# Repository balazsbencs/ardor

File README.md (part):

<h1 align="center">
  
</h1>

Ardor is a standalone Raspberry Pi guitar-processing platform with a realtime
audio engine, touchscreen/footswitch UI, preset storage, a browser-based manager
served by the device, and a reproducible Buildroot firmware image.

The signal chain supports Neural Amp Modeler `.nam` files, cabinet impulse
responses, 35 hosted modulation/delay/reverb effects, compression, noise
gating, five-band parametric EQ with high-pass and low-pass filters, global gain,
and a safety limiter. The same
LVGL interface runs in the SDL desktop simulator and on the Raspberry Pi Touch
Display 2.

The pedal is an appliance rather than a plugin host. Plugin formats and an OTA
update workflow are outside the current scope.

<table>
  <tr>
    <td width="50%"></td>
    <td width="50%"></td>
  </tr>
  <tr>
    <td align="center"><sub>Build the chain from neural amps, cabs and effects</sub></td>
    <td align="center"><sub>Four-track looper on the footswitches</sub></td>
  </tr>
</table>

## What You Need

To build an Ardor pedal, start with a Raspberry Pi 4 (the 1 GB model is
enough), its USB-C power supply, and a microSD card for the Ardor image. Put
the Raspberry Pi Codec Zero audio board on top of the Pi, and connect the 5 inch
Raspberry Pi Touch Display 2 with its ribbon cable. A guitar cannot connect
directly to the Codec Zero, so you also need the small Ardor guitar input buffer
board. You can order it from JLCPCB with the parts already fitted (see
[Guitar Input Buffer](#guitar-input-buffer)), and it runs from a normal 9 V
guitar pedal power supply. For a complete floor pedal, add four momentary
footswitches, one rotary knob (encoder) for the master volume, one 1/4 inch
input jack, two 1/4 inch output jacks, and a case. You can 3D print the case
from [`enclosure.openscad`](enclosure.openscad). You need a soldering iron for
some basic soldering of the jacks, switches, and wires. MIDI and expression
pedal inputs come later. The [hardware assembly guide](docs/hardware-assembly.md)
shows all the wiring.

## Community

See [CONTRIBUTING.md](CONTRIBUTING.md) before proposing changes. Contributors
are recognized in [CONTRIBUTORS.md](CONTRIBUTORS.md), and suspected
vulnerabilities should be reported privately according to
[SECURITY.md](SECURITY.md).

## Requirements

- CMake 3.20+
- C++20 compiler
- Single-precision FFTW development files (`libfftw3-dev` on Debian/Ubuntu,
  `brew install fftw` on macOS). Custom SDK paths can be supplied through
  `ARDOR_FFTW_INCLUDE_DIR` and `ARDOR_FFTW_LIBRARY` at CMake configure.
- Git access during CMake configure, for `miniaudio` and `NeuralAmpModelerCore`
- SDL2 for the LVGL desktop simulator (`ARDOR_UI_BACKEND=sdl`)
- macOS for desktop testing, or Linux for target-style builds
- Optional: Go for the manager daemon, Node.js 24 via `nvm use` for the manager
  web app, and Docker for the Buildroot firmware image
- Local test assets:
  - `models/test.nam`
  - `irs/test.wav`
  - optional `reverb-irs/test.wav`
  - optional dry input WAV for offline rendering

Real `.nam` and IR files are ignored by git. Keep licensed/user-provided assets local unless redistribution is allowed.

The POG3 DSP links FFTW, which is GPL-2.0-or-later. Distribution of FFTW-linked
binaries must comply with that license; the repository's MIT license does not
cover FFTW. See [the FFT backend notes](docs/pog3-fft-backend-evaluation.md).

## Guitar Input Buffer

A passive guitar must pass through the Ardor input buffer before it reaches
the Codec Zero. The repository contains the separate, minimal KiCad project
in [`buffer/`](buffer/).

You can order a board with the SMD parts fitted through
[JLCPCB](https://jlcpcb.com/). Upload these files from
[`buffer/jlcpcb/production_files/`](buffer/jlcpcb/production_files/):

- [`GERBER-buffer.zip`](buffer/jlcpcb/production_files/GERBER-buffer.zip) for the PCB files.
- [`BOM-buffer.csv`](buffer/jlcpcb/production_files/BOM-buffer.csv) for the parts list.
- [`CPL-buffer.csv`](buffer/jlcpcb/production_files/CPL-buffer.csv) for the part placement list.

The production files do not include audio jacks, wires, connectors, or the
enclosure. Add these parts after the board arrives. Connect the guitar jack to
`GUITAR_IN` and connect `GUITAR_OUT` to the Codec Zero input. Follow the buffer
schematic for power and ground connections.

## Preset Storage

Preset files live under the data root in bank/slot folders, for example:

- `presets/bank-000/preset-0.json`

Block assets inside preset JSON stay relative to that same data root, such as `models/clean.nam`, `irs/open-back.wav`, or `reverb-irs/small-room.wav`. Cabinet IRs and convolution reverb IRs use separate directories. Existing convolution presets that reference an installed `irs/` asset remain compatible, while new reverb selections use `reverb-irs/`. Absolute paths and `..` traversal are rejected. Real `.nam` models and IRs stay local and are not committed unless redistribution is allowed.

Convolution reverb exposes **Reverb time** in the pedal and manager editors.
It scales the recorded decay from 25% to 100%; 100% preserves the original IR.
For example, a two-second decay becomes approximately one second at 50%.
The processor estimates RT60 from the loaded stereo IR and applies a decay
envelope without changing reflection timing, pitch, or embedded pre-delay.
IRs shorter than 100 ms, silent impulses, and responses without a reliable
decay estimate stay unchanged. The four-second IR cap still applies.
Live edits crossfade using the existing convolution history. This control is
shared across scenes; convolution-kernel preparation runs on the control thread.

### Scenes

Version-4 presets contain four named scenes. A scene changes prepared parameter
values, qualified effect bypass states, input gain, WDW lane values, and a
post-rig trim without rebuilding the audio engine. Each scene can switch
instantly or transition over 0.1–10 seconds.

On a scene-enabled preset, hold FS3 + FS4 for 600 ms to enter or leave the
Scenes layer. The four footswitches then recall the four scene plates. Hold
FS1 + FS2 for one second to open the muted tuner. The touchscreen and Manager
show the live scene separately from the scene being edited.

Qualified delay and reverb blocks offer shared **Cut** and **Let ring** bypass
policies. Let ring stops new wet input while the existing decay continues for a
bounded lifetime. Version-4 data survives preset copies, backup/restore, hosted
read/write, and Looper source snapshots. Explicit flattening resolves one scene,
folds its trim into output gain, removes scene-only mappings, and produces the
minimum compatible ordinary preset version. See
[`presets/bank-002/preset-1.json`](presets/bank-002/preset-1.json) for an
asset-free example.

### Supported Parameters

Preset globals:

- `global.inputGainDb`: input gain before NAM.
- `global.outputGainDb`: output gain after cab.
- `global.safetyLimitDb`: limiter ceiling, where `-1.0` is the default. Stored and applied, but not editable from the UI — it is a protective clipper, not a tone control.

NAM block params:

- `params.inputMode`: stereo-to-mono routing at the NAM input: `"sum"` averages left and right (default), `"left"` uses the left/mono channel, and `"right"` uses the right channel.
- `params.useNano`: when `true`, selects the embedded nano submodel to reduce CPU usage; missing or `false` selects the full model.

Pass `--input-reference-dbu DBU` to map the audio interface's measured analog
input reference to NAM models that contain `input_level_dbu` metadata. The
reference is the analog dBu RMS level that produces a 0 dBFS-peak 1 kHz sine at
the ADC. Models without the metadata retain unity input scaling. Preset input
gain remains available as a separate creative or corrective control.

Cab block params:

- `params.levelDb`: cab level before output gain.
- `params.mix`: `0.0` dry after-NAM signal, `1.0` full cab signal.

Dual Amp is one draggable `type: "dualAmp"` block with two fixed parallel
lanes. Both lanes receive the selected mono input; the left NAM → IR lane feeds
only the left output and the right NAM → IR lane feeds only the right output.
It uses:

- `params.inputMode`: `"sum"` (default), `"left"`, or `"right"`.
- `params.leftNamAsset` / `params.rightNamAsset`: relative `.nam` asset paths.
- `params.leftIrAsset` / `params.rightIrAsset`: relative IR asset paths.
- `params.leftUseNano` / `params.rightUseNano`: per-model nano selection.
- `params.leftCabLevelDb` / `params.rightCabLevelDb`: `-60..12` dB.
- `params.leftCabMix` / `params.rightCabMix`: `0.0..1.0`.
- `params.leftPolarityInvert` / `params.rightPolarityInvert`: whole-lane polarity.

An enabled Dual Amp block cannot be combined with standalone NAM or cabinet
blocks in the same preset. Existing version-1 serial presets remain compatible.

Dual Rig generalizes that fixed block to two independent child chains. It is a
version-2 preset block and remains one draggable item in the outer chain:

```json
{
  "version": 2,
  "blocks": [{
    "id": "rig-1",
    "type": "dualRig",
    "enabled": true,
    "asset": "",
    "params": {
      "inputMode": "sum",
      "leftLevelDb": 0,
      "leftPolarityInvert": false,
      "rightLevelDb": 0,
      "rightPolarityInvert": false
    },
    "lanes": {
      "left": { "blocks": [
        {"id":"left-nam","type":"nam","enabled":true,"asset":"models/clean.nam","params":{}},
        {"id":"left-cab","type":"cab","enabled":true,"asset":"irs/open.wav","params":{}},
        {"id":"left-chorus","type":"mod","enabled":true,"asset":"","params":{"mode":"chorus"}}
      ]},
      "right": { "blocks": [
        {"id":"right-nam","type":"nam","enabled":true,"asset":"models/crunch.nam","params":{}},
        {"id":"right-cab","type":"cab","enabled":true,"asset":"irs/closed.wav","params":{}},
        {"id":"right-delay","type":"delay","enabled":true,"asset":"","params":{"mode":"digital"}}
      ]}
    }
  }]
}
```

Both lanes receive the same selected mono input. Each lane is processed in its
declared order; the left lane's left output and the right lane's right output
are retained at the fixed merge. Child block IDs are globally unique, both
lanes must be non-empty, and split blocks cannot be nested. Version-1 presets
and the fixed `dualAmp` block remain supported.

Daisy effect blocks use no asset path and store catalog-defined normalized
`0.0..1.0` parameters. The built-in catalog currently contains 35 modes:

- 13 modulation/special effects: chorus, flanger, rotary, vibe, phaser,
  vintage/pattern tremolo, poly octave, auto swell, filter, formant,
  quadrature, and destroyer.
- 10 delays: digital, tape, dual, filter, lo-fi, bucket-brigade, duck,
  pattern, swell, and tremolo.
- 12 reverbs: room, hall, plate, spring, bloom, cloud, shimmer, chorale,
  nonlinear, swell, magneto, and reflections.

Each mode uses semantic labels, physical-value formatting, defaults, and
discrete choices from `src/daisyfx/DaisyFxCatalog.cpp`. Compressor blocks use
`type: "dynamics"` with mode `compressor`.

Noise Gate blocks use `type: "dynamics"` with mode `noise_gate`. Their numeric
parameters are `threshold_db`, `reduction_db`, `attack_ms`, `hold_ms`,
`release_ms`, `hysteresis_db`, and `sidechain_hpf_hz`. Detection is
stereo-linked and the gate adds no lookahead latency.

The Ardor-maintained Daisy effect engine lives under `src/daisyfx/hosted/`.
Its upstream origin and license are preserved there; host adaptation and effect
implementation now live together under `src/daisyfx/`.

Five-band EQ blocks use `type: "eq"`, mode `parametric_eq_5`, and five entries
in `params.bands`. Each band stores `enabled`, `frequency_hz` (20–20,000 Hz),
`q` (0.1–18), and `gain_db` (-18 to +18 dB). Missing fields receive indexed
band defaults; saved presets always contain exactly five complete bands. The
surrounding `high_pass` and `low_pass` filters store `enabled`, `frequency_hz`,
`q`, and `slope_db_per_octave` (6, 12, 18, or 24; default 12).

## Build

Desktop build with the SDL UI:

```sh
cmake -S . -B build-sdl -DARDOR_UI_BACKEND=sdl -DCMAKE_BUILD_TYPE=Release
cmake --build build-sdl -j
```

Primary executables include:

- `build-sdl/pedal-poc` — offline/realtime engine and integrated UI
- `build-sdl/pedal-ui-sim` — desktop-only LVGL simulator
- `build-sdl/audio-probe` — audio-device probe

An opt-in standalone desktop application is being developed for Mac first.
Configure with `-DARDOR_BUILD_DESKTOP=ON` and the SDL backend to build
`ardor-desktop` (`Ardor.app` on Mac). See the
[desktop prototype instructions](apps/ardor-desktop/README.md) for audio setup,
user-library storage, validation, and current limitations.

The full-chain [CLAP beta](plugins/ardor-clap/README.md) is an optional follow-up
with `-DARDOR_BUILD_CLAP_PLUGIN=ON`. It supports 48 kHz DAW sessions and
per-project full-chain state. Beta 2 includes the shared Ardor editor on Mac
with `-DARDOR_UI_BACKEND=memory`; Linux uses host-generated controls. It is
separate from the Whammy plugin.

The [standalone NAM loader](plugins/nam-clap/README.md) provides a smaller CLAP
effect for macOS Apple Silicon, with a native editor for the model's own controls
and selectable Nano/Standard tiers when exported together. Build it separately
with `cmake -S plugins/nam-clap -B build-nam-clap -DCMAKE_BUILD_TYPE=Release`.

For a headless build, configure with `-DARDOR_UI_BACKEND=none`. The Pi firmware
uses the `fbdev` backend through the Buildroot package.

## Test

```sh
ctest --test-dir build-sdl --output-on-failure
```

The CTest suite covers preset parsing and activation, realtime-chain behavior,
Daisy effects and automation, compressor, noise gate, parametric EQ, the
four-track looper and its persistent store, tuner and control gestures, UI
models/LVGL interaction, audio-device enumeration, and reload stress. The
looper timing benchmark is intentionally separate from CTest:

```sh
cmake --build build-sdl --target pedal-looper-bench
./build-sdl/pedal-looper-bench --block-sizes 64,128 --warmup 100 --iterations 1000
```

Host results are useful for regressions, but do not replace the Raspberry Pi 4
acceptance benchmark and ten-minute production-backend soak. Hardware latency,
Codec Zero routing, and subjective audio validation remain device-level checks.

## List Audio Devices

```sh
./build-sdl/pedal-poc --devices
```

On macOS with a Behringer U-Phoria UMC22, it usually appears as `USB Audio CODEC`.

## Offline Render

Preset files use relative asset paths under `--data-root`.

Preset-driven offline render:

```sh
./build-sdl/pedal-poc \
  --offline \
  --preset ./presets/bank-000/preset-0.json \
  --data-root . \
  --input ./dryguitar.wav \
  --output ./wet.wav
```

Bypass NAM and test only IR/output rendering:

```sh
./build-sdl/pedal-poc \
  --offline \
  --ir irs/test.wav \
  --input /path/to/dry-guitar.wav \
  --output /tmp/ardor-wet.wav \
  --bypass-nam
```

Run NAM plus IR:

```sh
./build-sdl/pedal-poc \
  --offline \
  --model models/test.nam \
  --ir irs/test.wav \
  --input /path/to/dry-guitar.wav \
  --output /tmp/ardor-wet.wav
```

Input and IR WAV files must be 48 kHz.

## Realtime Run

List devices first:

```sh
./build-sdl/pedal-poc --devices
```

Example output:

```text
Playback devices:
  [1] USB Audio CODEC
Capture devices:
  [1] USB Audio CODEC
```

Run with explicit UMC22 routing:

```sh
./build-sdl/pedal-poc \
  --realtime \
  --model models/test.nam \
  --ir irs/test.wav \
  --sample-rate 48000 \
  --block-size 64 \
  --capture-device 1 \
  --playback-device 1 \
  --input-channel right \
  --output-channel both \
  --input-gain-db -12 \
  --output-gain-db -6 \
  --safety-limit-db -1
```

Preset-driven realtime run:

```sh
./build-sdl/pedal-poc \
  --realtime \
  --preset ./presets/bank-000/preset-0.json \
  --data-root . \
  --capture-device 1 \
  --playback-device 1 \
  --input-channel left \
  --output-channel both \
  --block-size 64 \
  --ir-samples 8192
```

Stop with `Ctrl-C`.

### Realtime preset slot switching

Slot-based realtime mode loads presets from `--data-root`:

```sh
./build-sdl/pedal-poc --realtime --data-root . --bank 0 --slot 0 \
  --capture-device 1 --playback-device 1 --input-channel left --output-channel both \
  --block-size 64 --ir-samples 8192
```

While it is running, type `0`, `1`, `2`, or `3`, then Enter, to switch presets in the current bank. The app reloads outside the audio callback, restarts the realtime device, and resumes telemetry.

Use `--input-channel left` for input 1 and `--input-channel right` for input 2. On the UMC22, the instrument input is commonly the right/second capture channel.

Realtime mode uses the full IR by default through partitioned convolution. Use `--ir-samples N` to cap long IRs when comparing performance or testing slower hardware.

The output safety limiter is on by default at `-1 dBFS`; adjust it with `--safety-limit-db DB` or disable it with `--no-safety-limit`.

If the sound is overloaded, reduce `--input-gain-db` first. That lowers the signal before NAM. If the amp character is right but the final output clips, reduce `--output-gain-db`.

Add `--clip-debug` to print interval peaks at the input-gain boundary, after every effect block, and immediately before the safety limiter. For example:

```text
levels input=-7.2dBFS nam:amp=1.4dBFS CLIP[38] ir:cab=-0.8dBFS output=-1.1dBFS limiter=[122] first=nam:amp
```

`CLIP[n]` counts frames above 0 dBFS during the interval, and `first=` identifies the earliest boundary that crossed full scale. This distinguishes signal-level overload from intentional NAM distortion: if `input` or `nam:...` is first, reduce input gain; if `ir:...` is first, reduce cabinet level; if only `output` or `limiter` is active, reduce output gain or master volume. The meter observes processor boundaries—it cannot label the intentional nonlinear distortion inside a NAM model as clipping.

With `--clip-debug --ui`, the touchscreen status bar shows the same diagnosis: red `CLIP` with the first stage and peak, amber `LIMIT` when only the safety limiter engages, or green `LEVEL OK`. It refreshes once per second.

Realtime status prints once per second:

```text
callbacks=28125 over=0 over%=0.00 max=0.41ms avg=0.23ms budget=1.33ms
```

`over` counts callbacks that took longer than the audio budget. For `--block-size 64` at 48 kHz, the callback budget is about `1.33 ms`.

Dual Amp and Dual Rig always have a sequential fallback: the callback processes
the complete left lane and then the complete right lane. On a four-core Pi,
enable the optimized path with
`--parallel-rigs --audio-cpu 2 --rig-worker-cpu 3`. This keeps the callback at
`SCHED_FIFO/70` on CPU 2 and runs a persistent right-lane worker at
`SCHED_FIFO/69` on CPU 3; the callback processes the complete left lane
concurrently and joins the worker once at the fixed merge. Effects before and
after the parallel block still run serially on the callback thread. The two CPU
arguments are required and must differ. If the worker cannot obtain its
requested realtime policy or affinity, the rig reports the failure and uses
sequential processing. The older `--parallel-dual-amp` and
`--dual-amp-worker-cpu` spellings remain accepted.

The Buildroot image enables that layout by default through
`PARALLEL_RIGS=1`, `AUDIO_CPU=2`, and `RIG_WORKER_CPU=3` in
`/etc/ardor-pedal.env`. WDW adds two independent lane workers; the image
defaults to `WDW_DRY_WORKER_CPU=0` and `WDW_WET_WORKER_CPU=1` and passes them as
`--wdw-dry-worker-cpu` / `--wdw-wet-worker-cpu`. These assignments keep the
audio callback, legacy dual-rig worker, and both WDW lanes on distinct Pi 4
cores. The UI and non-audio work remain normal-priority Linux tasks; the
realtime DSP threads preempt them on their assigned cores.

Measure that layout on a running pedal over SSH:

```sh
./scripts/measure-device-performance.sh --duration 30 192.168.88.17
```

The probe reports whole-core utilization and headroom, per-thread CPU usage,
last CPU, affinity, realtime policy and priority, migrations, temperature, and
CPU clock range. Production builds also publish an atomic snapshot at
`/run/ardor-pedal.telemetry`; the probe uses its before/after counters to check
callback overruns, scheduling gaps, parallel-worker deadline misses,
non-finite DSP blocks, block-size mismatches, and overload bypass. It checks
that the callback is `SCHED_FIFO/70` on CPU 2. With a Dual Amp or Dual Rig
preset active, require and validate the `SCHED_FIFO/69` worker on CPU 3:

```sh
./scripts/measure-device-performance.sh \
  --duration 60 --require-worker 192.168.88.17
```

The local wrapper streams
`scripts/device-performance-remote.sh` to BusyBox `sh`; it does not install
anything or modify the pedal. Use `ARDOR_PI_HOST`, `ARDOR_SSH_USER`, and
`ARDOR_SSH_OPTS` for repeatable lab configuration. Passwords are handled by
OpenSSH and are never stored by the scripts. The final pass/fail verdict covers
thread placement, realtime scheduling, and audio/DSP fault counters;
utilization, headroom, clock, and thermal values remain measurements to compare
between presets and builds.

Realtime telemetry is shared between CLI and UI. The known-good baseline remains `--block-size 64 --ir-samples 8192`. If the overload bypass latches, the CLI prints `bypassed=1` and the UI shows `BYPASS`.

First target settings:

- sample rate: `48000`
- preferred block size: `64`
- fallback block size: `128`
- input: mono
- output: stereo
- round-trip latency goal: under `10 ms`

Chain layout contract: NAM and cabinet blocks are mono stages. A NAM block may follow
stereo effects and folds its input according to `params.inputMode`; its mono output is
copied to both channels. Cabinet blocks must still precede stereo effects. Dual Amp
and Dual Rig establish stereo with their hard-left/hard-right lanes. Inside a Dual
Rig, the same ordering rules apply independently to each lane. Modulation preserves
stereo input. The hosted delay and reverb effects preserve the stereo dry field but
sum their wet input to mono before producing their vendor-defined stereo wet output.

Hardware controls on Raspberry Pi use Linux input events:

```sh
./build-sdl/pedal-poc --realtime --data-root . --bank 0 --slot 0 \
  --control-device /dev/input/event-footswitches \
  --control-device /dev/input/event-encoder \
  --block-size 64 --ir-samples 8192
```

The app maps `KEY_F1` through `KEY_F4` to preset slots and relative encoder
movement to master output volume. Tap FS1 through FS4 to select the matching
slot. Hold FS2 for 600 ms to move down one bank, or FS4 for 600 ms to move up
one bank; bank changes keep the current slot number. Hold the two left switches
(`KEY_F1` + `KEY_F2`) together for one second to mute the output and open the
tuner; press any footswitch to exit without changing presets. The touchscreen
provides the same tuner flow through the preset-screen Tuner button and
tuner-screen Exit button.

### Four-Track Looper

Select a preset, then press **Looper** on the preset screen. That preset remains
locked until the loop session is closed, and all recorded audio captures its
processed stereo output before master volume and the safety limiter. The four
large track plates select the working track. The four footswitches keep fixed
performance roles:

- FS1 toggles one-level undo/redo for the selected track;
- tap FS2 to select the next track, or hold it to clear the selected track;
- FS3 starts/stops the first recording or an overdub, and FS4 mutes/unmutes the
  selected track;
- hold FS1 + FS2 to pause and enter the tuner; leaving the tuner resumes a loop
  that was previously running;
- later empty tracks arm and begin recording together at the next master-loop
  boundary, so all four layers stay synchronized;
- the touchscreen adds global pause/resume, New/Save/Load/Close, track
  selection, and per-track level/balance controls.

Save and Load are available only while paused. A saved set contains the four
effective stereo tracks, mix settings, loop length, and a snapshot of the
source preset under `loops/<32-character-id>/`. Saving runs outside the audio
callback and publishes the manifest last, so a failed replacement preserves
the previous durable revision. Closing a session releases its preset lock and
restores the preset that was active before a recalled loop.

The planned TRS-A MIDI and expression-pedal interface, message mapping, GPIO
allocation, and preset expression schema are documented in
[`docs/midi-expression-control.md`](docs/midi-expression-control.md). Its
native KiCad schematic is under [`hardware/control-io`](hardware/control-io/README.md).

## Manager Daemon

The REST manager daemon lives in `services/managerd`. It manages `.nam`, `.wav`,
and preset files without doing management work in the realtime process. Asset
uploads queue a catalog refresh for the pedal UI. Applying a saved slot queues
a live engine swap, handled by the pedal management loop without restarting the
audio process; a short muted transition protects the active audio callback.

The hosted HTTPS manager architecture and delivery plan are specified in
[`docs/hosted-manager-architecture.md`](docs/hosted-manager-architecture.md).
Its Phase 1 foundation includes the shared UI transport contract, durable
device identity, versioned wire schemas, and a reconnecting outbound cloud
agent. Phase 2 adds a SQLite-backed hosted control plane, account recovery,
device presence, and physically confirmed claiming. Phase 3 adds hosted preset
list/read/save/apply operations with durable idempotency. Phase 4 adds bounded
asset streaming and server-side TONE3000 integration. Phase 5 adds device-local
accounts, recoverable reset flows, and mDNS discovery.

Run locally without auth:

```sh
cd services/managerd
ARDOR_API_AUTH=off \
ARDOR_DATA_ROOT=../.. \
ARDOR_API_BIND=127.0.0.1 \
ARDOR_API_PORT=8080 \
go run ./cmd/ardor-managerd
```

The device status endpoint is:

```sh
curl http://127.0.0.1:8080/api/device
```

The daemon also serves a device-hosted build of the React manager from `/`.
When loaded from the daemon, the manager connects to the same origin
automatically, so any browser on the network can manage the pedal:

```sh
cd apps/manager
nvm use
npm run build:device

cd ../../services/managerd
ARDOR_API_AUTH=off ARDOR_DATA_ROOT=../.. go run ./cmd/ardor-managerd
```

Open `http://127.0.0.1:8080` for local development, or the corresponding
device address on the local network. On supported networks, the daemon also
advertises `_ardor-manager._tcp` and a stable hostname derived from the device
identity. With the default port, use
`http://ardor-<first-8-device-id-characters>.local:8080`; a production image
that binds the daemon to port 80 can omit the port. Set `ARDOR_MDNS=off` only
when discovery must be disabled. The generated bundle is embedded in the
`ardor-managerd` binary so it remains available without internet access.

For repeat LAN deployments, `scripts/deploy-lan.sh` uses a local Docker builder
image (`ardor-builder:ubuntu-24.04`) after its first run, avoiding a fresh APT
installation each time. Normal deploys reuse Buildroot's package output; set
`ARDOR_PEDAL_DIRCLEAN=1` only when a clean pedal-package rebuild is needed.
Use `ARDOR_APT_MIRROR=http://hu.archive.ubuntu.com/ubuntu` to build the cached
image from the Hungarian Ubuntu mirror.

Auth is enabled by default when no environment override is supplied. On first
start, the pedal displays a short-lived setup code. Open the device-hosted
manager on a trusted LAN and enter that code to choose one local username and
password. Passwords are stored as Argon2id hashes; browser sessions use an
`HttpOnly`, `SameSite=Strict` cookie and mutation requests require a matching
local Origin and Host. Direct LAN access uses HTTP, so the UI clearly warns
that it is intended for trusted networks. `ARDOR_API_AUTH=off` is for explicit
development/testing use and no static API token is required.

Set `TONE3000_CLIENT_ID` on the device to enable **Browse TONE3000** under
Assets → NAM models. Ardor supports NAM A2 captures only. The device starts
TONE3000's LAN OAuth relay using its Wi-Fi address, so the browser or phone
used to sign in must be on the same trusted Wi-Fi network as the pedal. OAuth
credentials remain in device memory only for the one 15-minute selection and
the selected model is saved through the normal local asset path. The
publishable `t3k_pub_…` client ID may be deployed on the device; never deploy a
TONE3000 secret key. `TONE3000_BASE_URL` defaults to
`https://www.tone3000.com` and is useful only for development overrides.
LAN deployments preserve an existing TONE3000 configuration. If the client ID
is missing, they restore the firmware's publishable default; set
`TONE3000_CLIENT_ID` when deploying to override it.

The Security & reset settings can sign out, reset only local access, or request
a factory reset. Resetting local access removes the username, password hash,
and all sessions while preserving presets, assets, Wi-Fi, and cloud state. A
factory reset must be approved on the pedal with footswitch 1 (footswitch 4
cancels); it clears device-local user data while preserving the stable device
identity and its reset audit record. A durable reset marker makes an interrupted
factory reset resume deterministically after restart.

The outbound cloud agent is disabled by default. A control-plane deployment can
enable it with `ARDOR_CLOUD_ENABLED=on` and an HTTPS origin in
`ARDOR_CLOUD_URL`. Preset reads are available over an authenticated claimed
device connection. Preset save/apply remains opt-in per pedal with
`ARDOR_CLOUD_REMOTE_MUTATIONS=on`; only the four allowlisted preset operations
are accepted. The generated Ed25519 identity is stored under
`<ARDOR_DATA_ROOT>/identity/device.json` with mode `0600`.

## Hosted Control Plane

The initial control plane in `services/controlplane` is a single Go service
with an embedded migration set and a pure-Go SQLite driver. SQLite is the
intentional first-deployment choice: the server has one active instance and a
single writer, so PostgreSQL would add operations without adding useful
capacity yet. The repository boundary leaves a future database migration open.

Run the API locally over explicitly enabled development HTTP:

```sh
cd services/controlplane
ARDOR_INSECURE_HTTP=on \
ARDOR_PUBLIC_ORIGIN=http://127.0.0.1:8090 \
go run ./cmd/ardor-controlplane
```

Build the hosted browser application with the repository Node version:

```sh
cd apps/manager
nvm use
npm run build:hosted
```

Production deployment must expose that static bundle and `/v1` from the same
public HTTPS origin. Account sessions are `HttpOnly`, `SameSite=Strict`, secure
cookies; state-changing browser requests also require the exact public Origin.
Hosted preset save/apply requests carry UUID idempotency keys; completed
responses and audit events are persisted in the same SQLite transaction.

## Manager Web App

The React manager in `apps/manager` connects to `ardor-managerd` and provides
bank/slot browsing, drag-and-drop chain editing, block validation and
inspection, undo/redo, Save/Apply, asset upload/rename/delete, and light/dark
themes. The device serves it over LAN HTTP, so no installation is needed. There
is no desktop application.

Run the app against a device during development:

```sh
cd apps/manager
npm install
npm run dev
```

TONE3000 browsing of NAM captures is part of the hosted control-plane build.
The control plane holds the TONE3000 credentials; see
`services/controlplane/README.md`.

For local testing, run the Go daemon with auth disabled and use
`http://127.0.0.1:8080` as the manager base URL:

```sh
cd services/managerd
ARDOR_API_AUTH=off ARDOR_DATA_ROOT=../.. ARDOR_API_BIND=127.0.0.1 ARDOR_API_PORT=8080 \
go run ./cmd/ardor-managerd
```

## Legacy UI Mockup

The original static HTML concept remains available for design history:

```sh
open mockups/preset-ui/index.html
```

The LVGL implementation described below is the authoritative interface.

## Touch UI and LVGL Simulator

The touch UI includes:

- A four-slot preset screen with bank controls, master-volume status, Edit,
  direct Tuner entry, and a global Settings gear between **Bank+** and **Edit**.
- A touch-first Settings screen for changing Wi-Fi credentials without
  reflashing, choosing the panel palette, configuring MIDI/expression input,
  and selecting a 32, 64, or 128-sample audio buffer. Audio-buffer changes
  restart the supervised engine process before they take effect.
- A persistent footer with centered master volume and one-second audio-buffer
  headroom feedback calculated from recent callback time versus its deadline.
- A single left-to-right signal canvas with horizontal touch scrolling,
  per-preset scroll memory, dedicated block drag handles, and Input/Output
  jump controls.
- An asset drawer with separate All, Amps, Cabs, Utility, Modulation, Delays,
  and Reverbs filters. Utility contains compressor, Noise Gate, and EQ blocks.
- `+` insertion points between every top-level effect and between effects in
  each split lane. Top-level insertion offers `Split Left / Right`; lane
  insertion prevents nested split regions.
- Compact lane handles reorder effects within a rail or move them across the
  Left and Right rails; moving the final block out of a lane is rejected.
- Dual Rig presets render as an explicit `SPLIT`, separate color-coded `LEFT`
  and `RIGHT` rails, and a stereo `JOIN` instead of disguising routing as an
  ordinary effect card.
- Long chains remain on the same horizontal signal line and auto-scroll when a
  dragged block reaches either screen edge.
- Two-row, three-column parameter pages using large horizontal sliders with
  inline labels/values, plus a matching rectangular bypass control.
- A dedicated five-band parametric EQ editor with high-pass and low-pass stages,
  selectable 6–24 dB/oct slopes, and a live response graph.
- A muted tuner with note/frequency/cents guidance and both touchscreen Exit
  and footswitch exit.

Build and launch the desktop simulator with:

```sh
./scripts/build-sim.sh
```

In Edit mode, tap any `+` on the mono rail and choose **Split Left / Right** to
create a version-2 split region. The Split starts with NAM and IR in both
lanes, using the first installed model and IR when available. Tap a lane's `+`
to add another effect directly to that rail. Only one active Split is
supported, split regions cannot be nested, and existing standalone NAM/IR
blocks must be removed before inserting the Split.

`pedal-ui-sim` is a desktop-only tool. It does not wire footswitch GPIO, the encoder, Codec Zero, or realtime audio. For the integrated UI+audio experience use `pedal-poc --ui` (see below).

### LVGL simulator with preset files

The simulator can load the same preset files used by `pedal-poc`:

```sh
./build-sdl/pedal-ui-sim --data-root . --bank 0
```

It reads:

- `presets/bank-000/preset-0.json`
- `presets/bank-000/preset-1.json`
- `presets/bank-000/preset-2.json`
- `presets/bank-000/preset-3.json`

Built-in algorithms are listed first, then assets discovered from
`models/*.nam`, `irs/*.wav`, and `reverb-irs/*.wav`. Cabinet and
convolution reverb impulses stay in their own drawer categories. Compressor,
Noise Gate, EQ, and Daisy effects come from built-in catalogs. The simulator
saves chain edits only when Save is pressed.

## Integrated UI and Audio

Pass `--ui` to `pedal-poc` in slot mode to run the LVGL UI alongside the audio engine in a single process:

```sh
./build-sdl/pedal-poc \
  --realtime \
  --ui \
  --data-root . \
  --bank 0 --slot 0 \
  --capture-device 1 \
  --playback-device 1 \
  --input-channel left \
  --output-channel both \
  --block-size 64 --ir-samples 8192
```

The UI starts on the preset screen. On-device effect-chain edits preview
immediately: structural and discrete changes prepare and swap a replacement
engine, while supported continuous parameters are published live. Save only
persists the already-audible draft. Switching preset or bank with unsaved edits
asks whether to Save, Discard, or Cancel. Telemetry (callback count, overruns, bypass state) updates once
per second. Encoder master volume is reflected in the UI. Tuner mode shows the
detected note, frequency, cents offset, and flat/sharp guidance while keeping
the pedal output muted.

`--ui` requires `ARDOR_UI_BACKEND=sdl` (desktop default) or `ARDOR_UI_BACKEND=fbdev` (Pi). It has no effect on the non-slot realtime or offline paths.

## Buildroot Firmware Image

The repository contains a Buildroot external tree for a Raspberry Pi 4 pedal
image. The build pins and verifies Buildroot 2025.02.15, runs in a native Docker
container on Apple Silicon or x86_64, and preserves the validated Raspberry Pi
Linux 6.18 hardware stack.

Build the complete image from the repository root:

```sh
./scripts/build-image.sh
```

The resulting `sdcard.img` contains:

- `/usr/bin/ardor-pedal` and `/etc/init.d/S99ardor-pedal`.
- `/usr/bin/ardor-managerd` and `/etc/init.d/S98ardor-managerd`.
- `/etc/ardor-pedal.env`, `/etc/ardor-managerd.env`, and the Codec Zero mixer
  state.
- A read-only root filesystem and writable `/opt/ardor-pedal` data partition
  seeded with four presets.

See [BUILD.md](BUILD.md) for prerequisites, versioned-volume behavior, flashing,
rollback, troubleshooting, hardware checks, REST verification, and deferred
upgrade work.

## Hardware Validation

See [Hardware Assembly Guide](docs/hardware-assembly.md) for the current Codec
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
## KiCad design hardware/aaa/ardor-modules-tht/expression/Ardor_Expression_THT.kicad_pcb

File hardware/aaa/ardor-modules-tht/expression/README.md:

# Passive expression pedal / I2C ADC / HAND ASSEMBLY

T1 hand-assembly PCB: 110 × 85 mm. **Unbuilt engineering prototype.**

[KiCad project](Ardor_Expression_THT.kicad_pro) · [Manual BOM](BOM.csv) · [Schematic](review/schematic.pdf) · [Bare-board Gerbers](assembly/Ardor_Expression_THT-Gerbers.zip)

Fit an **Adafruit product 1085 ADS1115, STEMMA QT revision**, using two six-pin 2.54 mm sockets and mating headers, with the digital VDD/GND/SCL/SDA/ADDR/ALRT row toward the lower edge of the outlined module footprint. The VDD corner is the square carrier pad (U301 pad 8). Two header rows are 12.7 mm apart. Earlier Adafruit boards and generic blue modules have different layouts and are not substitutes. See the complete [breakout pin translation](../SOURCES.md#ads1115-breakout-pin-translation). Do not rotate it 180 degrees.

The purchased breakout already contains all small SMD parts. Only its ordinary header pins require soldering. AVDD/AGND and ALRT are deliberately not wired on the carrier. Leave the breakout's ADDR-to-VDD solder jumper **open**. JP302 must have one shunt: 1–2 selects 0x48, 2–3 selects 0x49. These are the same ADS1115 registers/addresses used by M1; no ADC-driver change is required.

Use a passive 10–100 kΩ expression pot; do not connect powered CV. JP301 needs **two** shunts: 1–3 plus 2–4 for tip wiper, or 3–5 plus 4–6 for ring wiper. TRS sleeve goes to J302.3. Change polarity with power off.

Leave **JP303 and JP304 unshunted initially**. The breakout has permanent onboard 10 kΩ SDA/SCL pull-ups; these jumpers control only the additional carrier 2.2 kΩ pair. With a Raspberry Pi's 1.8 kΩ pair, the effective resistance is approximately 1.53 kΩ before adding any other module. Add the carrier pair only after calculating total bus pull-up current and checking cable rise time. Removing the carrier shunts does not remove the breakout's pull-ups.

Supply 3.3 V / 15 mA. Commission without the breakout first: verify rail polarity at the socket, then fit the breakout and check I²C detection at 100 kHz. Select ±4.096 V PGA and 128 SPS, read AIN0 (wiper) and AIN1 (excitation reference), normalize AIN0/AIN1, calibrate endpoints and smooth. Test both polarity settings and open-cable behavior. Do not drive the pedal while the module is unpowered.

## Connector pin assignments

Directions are relative to this board. Standard header square pads identify pin 1. Read reference and pin numbers from the back silkscreen; mirrored CAD exports are labelled as back views.

### J302 — PASSIVE PEDAL INPUT / EXCITATION OUTPUT

| Pin | Net | Direction | Connect to |
|---|---|---|---|
| 1 | EXP_TIP | INPUT / OUTPUT | Passive expression socket tip; not a powered CV pedal. |
| 2 | EXP_RING | INPUT / OUTPUT | Passive expression socket ring; not a powered CV pedal. |
| 3 | GND | GROUND | TRS sleeve; pedal pot ground and enclosure bond. |

### J101 — 3V3 POWER INPUT + I2C TO HOST

| Pin | Net | Direction | Connect to |
|---|---|---|---|
| 1 | +3V3 | POWER INPUT | Positive output of the matching regulated supply. |
| 2 | GND | GROUND | Host or cable ground / 0 V. |
| 3 | SDA | INPUT / OUTPUT | Host I2C SDA data pin. |
| 4 | SCL | INPUT | Host I2C SCL clock pin. |

### JP301 — JUMPER ONLY: PEDAL POLARITY

| Pin | Net | Direction | Connect to |
|---|---|---|---|
| 1 | EXP_TIP | JUMPER | Fit a shunt to pin 3 for tip-wiper mode. |
| 2 | EXP_RING | JUMPER | Fit a shunt to pin 4 for tip-wiper mode. |
| 3 | EXP_WIPER | INPUT / JUMPER | Shunt 1-3 for tip wiper, or 3-5 for ring wiper. |
| 4 | EXP_EXC | OUTPUT / JUMPER | Shunt 2-4 for tip wiper, or 4-6 for ring wiper. |
| 5 | EXP_RING | JUMPER | Fit a shunt to pin 3 for ring-wiper mode. |
| 6 | EXP_TIP | JUMPER | Fit a shunt to pin 4 for ring-wiper mode. |

TIP: 1-3 + 2-4; RING: 3-5 + 4-6. Use TWO shunts; no external cable.

### JP302 — JUMPER ONLY: ADC ADDRESS

| Pin | Net | Direction | Connect to |
|---|---|---|---|
| 1 | GND | JUMPER | Shunt 1-2 selects address 0x48. |
| 2 | ADDR | CONTROL / JUMPER | Fit ONE shunt: 1-2 or 2-3. |
| 3 | +3V3_A | JUMPER | Shunt 2-3 selects address 0x49. |

1-2: 0x48; 2-3: 0x49. One shunt required; no external cable.

### JP303 — JUMPER ONLY: SDA PULLUP

| Pin | Net | Direction | Connect to |
|---|---|---|---|
| 1 | SDA_PULL | JUMPER | Shunt 1-2 only if the host has no SDA pull-up. |
| 2 | SDA | INPUT / OUTPUT / JUMPER | Same shunt; this is not a host cable connector. |

Fit 1-2 to enable. Remove if host already has a pull-up.

### JP304 — JUMPER ONLY: SCL PULLUP

| Pin | Net | Direction | Connect to |
|---|---|---|---|
| 1 | SCL_PULL | JUMPER | Shunt 1-2 only if the host has no SCL pull-up. |
| 2 | SCL | INPUT / JUMPER | Same shunt; this is not a host cable connector. |

Fit 1-2 to enable. Remove if host already has a pull-up.

## Assembly and files

Fit low-profile axial parts first, then sockets/headers and radial capacitors. Match diode bands, electrolytic polarity and IC notches to the PCB. Install the ICs or ADC breakout last. H1/H2 are 2.2 mm nonplated M2 mounting holes, not electrical terminals. Check enclosure clearance and capacitor/socket height: these boards are larger than M1.

Use the manual BOM and the bare-board Gerber/drill ZIP. There is no SMT assembly order. Front silkscreen shows component references; the front fabrication drawing shows package outlines and orientation; use the BOM for values. Back silk includes port functions and pin numbers. Native checks and package manifests are under `verification/`; they do not replace prototype measurements.

[Assembly accessories](assembly/accessories.csv) list sockets, shunts and panel items in addition to the PCB component BOM.

[Family guide](../README.md) · [Substitution sources](../SOURCES.md) · [Native validation](verification/validation.json)

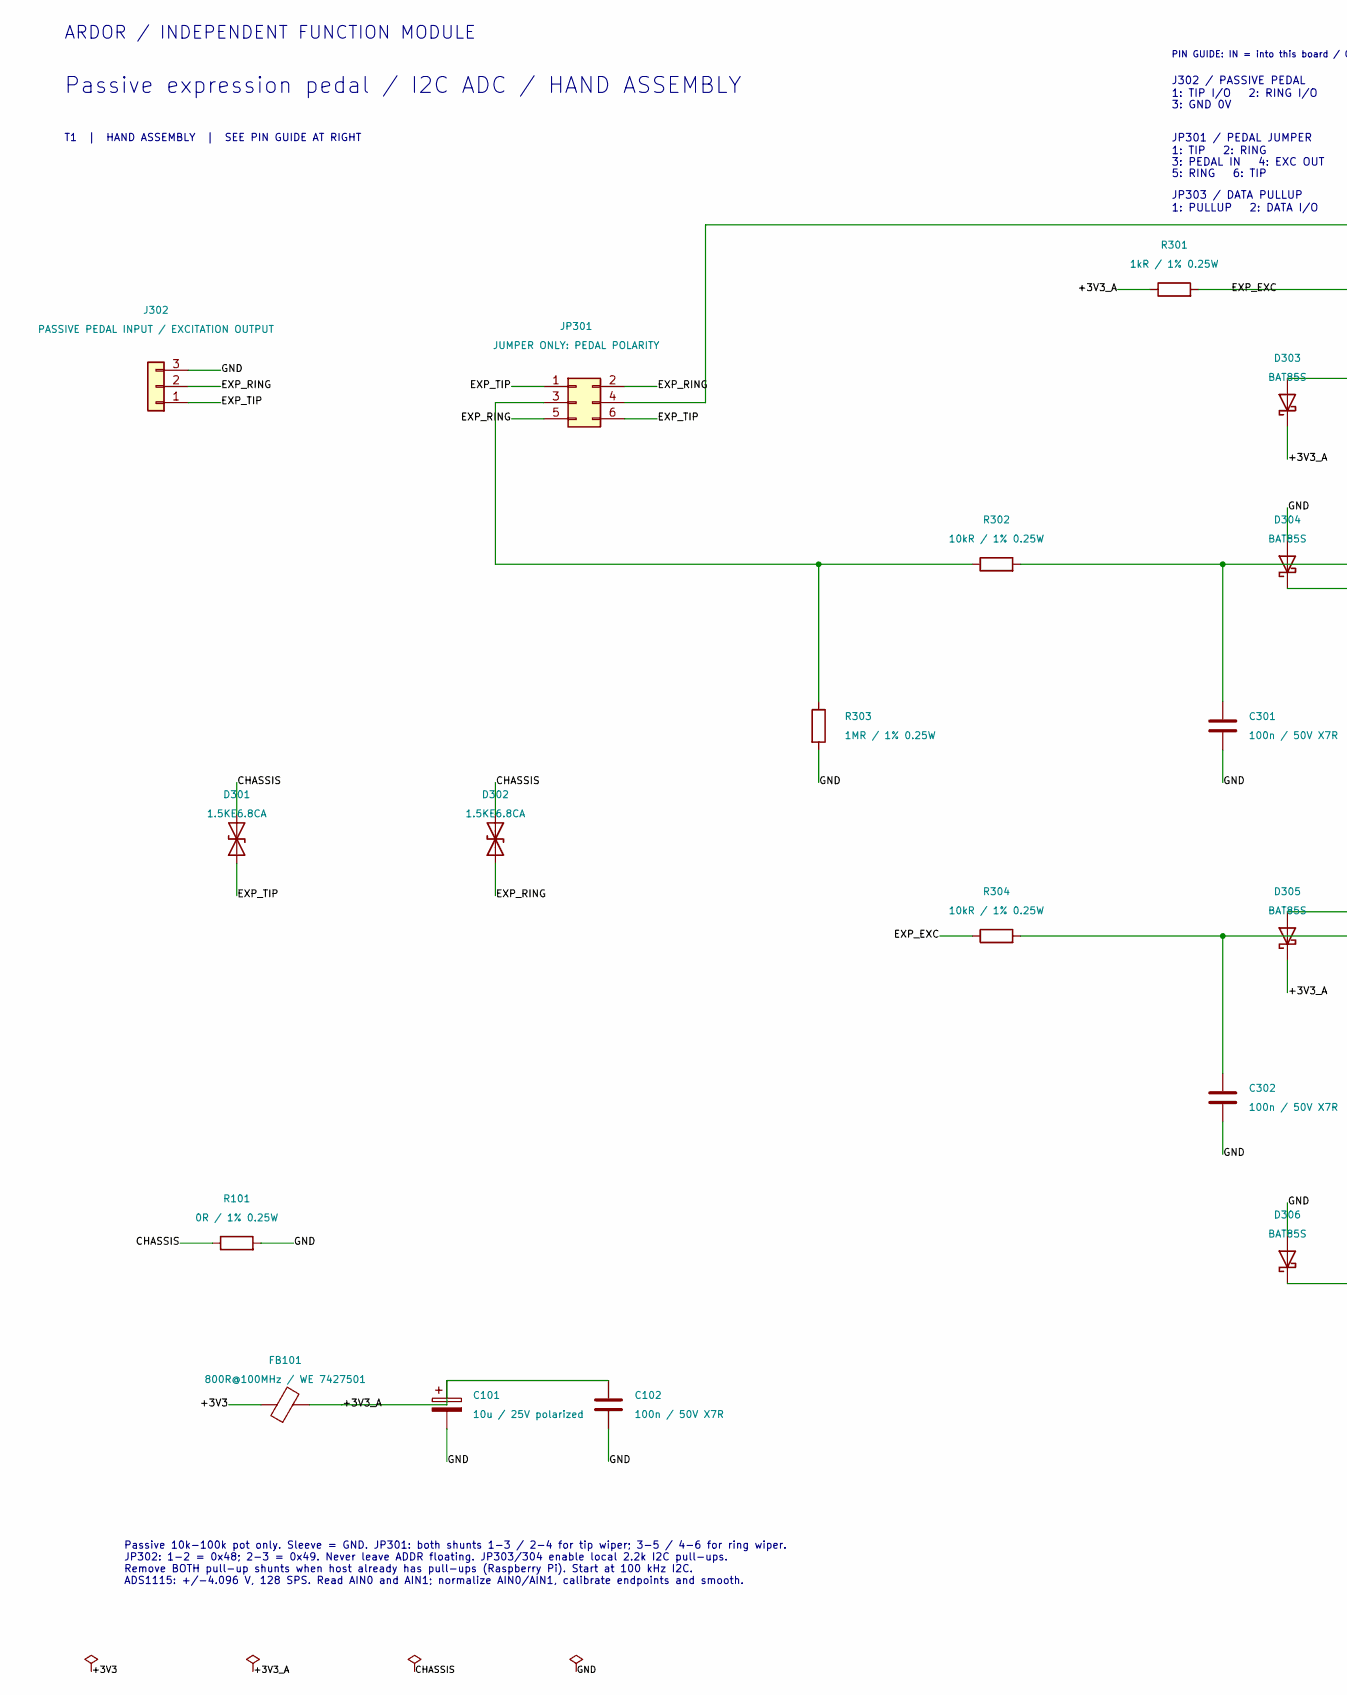
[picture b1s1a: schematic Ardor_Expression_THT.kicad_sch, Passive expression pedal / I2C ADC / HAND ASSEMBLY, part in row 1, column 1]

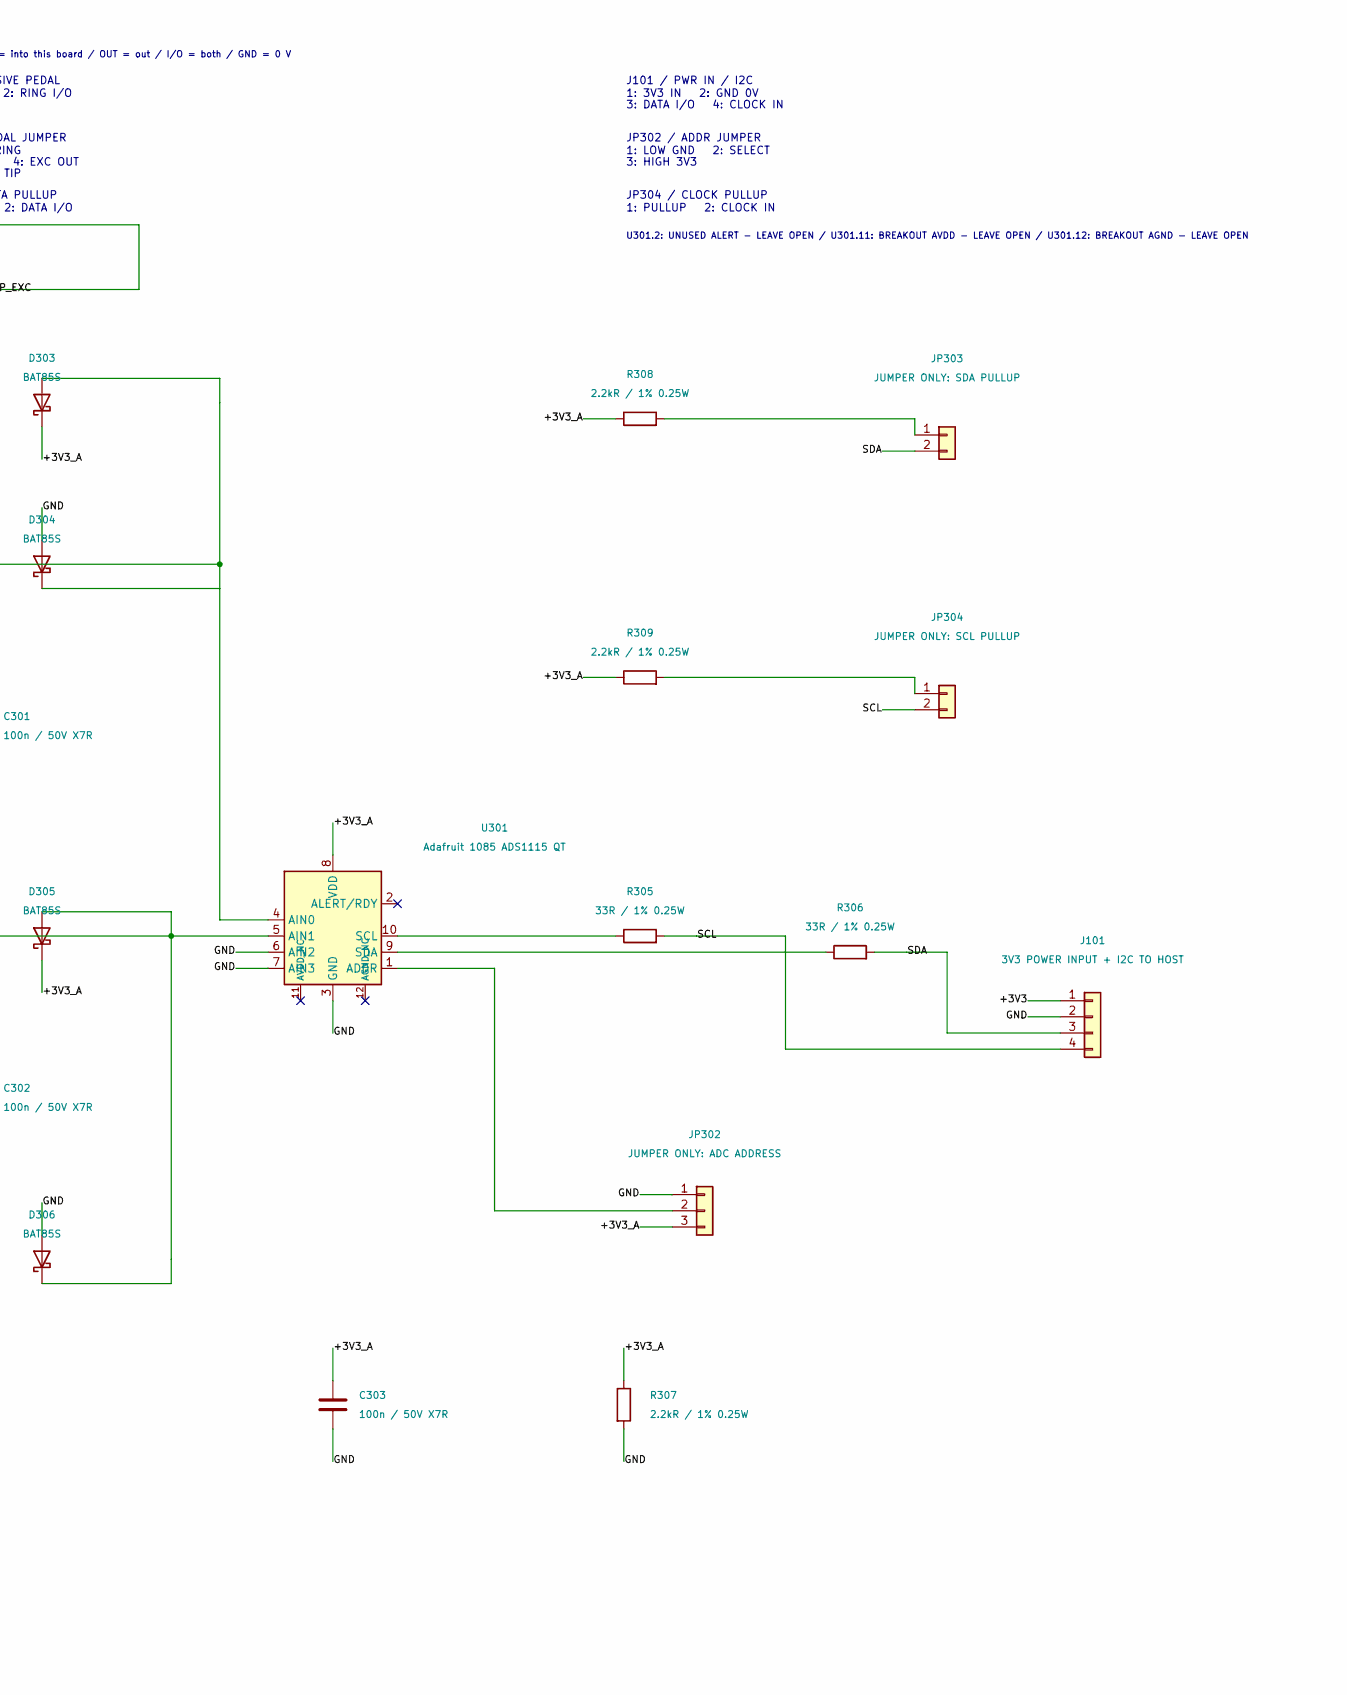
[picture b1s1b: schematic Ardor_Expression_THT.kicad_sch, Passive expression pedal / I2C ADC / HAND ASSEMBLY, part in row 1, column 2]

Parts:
C101: 10u / 25V polarized; CP_Radial_D6.3mm_P2.50mm; MPN Radial electrolytic 10uF 25V, D<=6.3mm 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
C102, C301, C302, C303: 100n / 50V X7R; C_Disc_D5.0mm_W2.5mm_P5.00mm; MPN 100nF 50V X7R radial, 5mm lead pitch
D301, D302: 1.5KE6.8CA; D_TVS_DC_1.5KE_P15.24mm; MPN DC Components 1.5KE6.8CA (HESTORE 100.4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
D303, D304, D305, D306: BAT85S; D_DO-35_SOD27_P7.62mm_Horizontal; MPN Vishay BAT85S-TAP
FB101: 800R@100MHz / WE 7427501; Ferrite_WE_7427501_P15.24mm; MPN Wurth Elektronik 7427501
J101: 3V3 POWER INPUT + I2C TO HOST; PinHeader_1x04_P2.54mm_Vertical; MPN PinHeader_1x04_P2.54mm_Vertical
J302: PASSIVE PEDAL INPUT / EXCITATION OUTPUT; PinHeader_1x03_P2.54mm_Vertical; MPN PinHeader_1x03_P2.54mm_Vertical
JP301: JUMPER ONLY: PEDAL POLARITY; PinHeader_2x03_P2.54mm_Vertical; MPN PinHeader_2x03_P2.54mm_Vertical
JP302: JUMPER ONLY: ADC ADDRESS; PinHeader_1x03_P2.54mm_Vertical; MPN PinHeader_1x03_P2.54mm_Vertical
JP303: JUMPER ONLY: SDA PULLUP; PinHeader_1x02_P2.54mm_Vertical; MPN PinHeader_1x02_P2.54mm_Vertical
JP304: JUMPER ONLY: SCL PULLUP; PinHeader_1x02_P2.54mm_Vertical; MPN PinHeader_1x02_P2.54mm_Vertical
R101: 0R / 1% 0.25W; R_Axial_DIN0207_L6.3mm_D2.5mm_P10.16mm_Horizontal; MPN Axial metal film 0Ω 1% 0.25W
R301: 1kR / 1% 0.25W; R_Axial_DIN0207_L6.3mm_D2.5mm_P10.16mm_Horizontal; MPN Axial metal film 1kΩ 1% 0.25W
R302, R304: 10kR / 1% 0.25W; R_Axial_DIN0207_L6.3mm_D2.5mm_P10.16mm_Horizontal; MPN Axial metal film 10kΩ 1% 0.25W
R303: 1MR / 1% 0.25W; R_Axial_DIN0207_L6.3mm_D2.5mm_P10.16mm_Horizontal; MPN Axial metal film 1MΩ 1% 0.25W
R305, R306: 33R / 1% 0.25W; R_Axial_DIN0207_L6.3mm_D2.5mm_P10.16mm_Horizontal; MPN Axial metal film 33Ω 1% 0.25W
R307, R308, R309: 2.2kR / 1% 0.25W; R_Axial_DIN0207_L6.3mm_D2.5mm_P10.16mm_Horizontal; MPN Axial metal film 2.2kΩ 1% 0.25W
U301: Adafruit 1085 ADS1115 QT; Adafruit_ADS1115_1085_STEMMA_QT; MPN Adafruit 1085 (STEMMA QT revision)

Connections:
/+3V3: FB101.1, J101.1
/+3V3_A: C101.1, C102.1, C303.1, D303.1 (K), D305.1 (K), FB101.2, JP302.3, R301.1, R307.1, R308.1, R309.1, U301.8 (VDD)
/CHASSIS: D301.2 (A2), D302.2 (A2), R101.1
/EXP_EXC: JP301.4, R301.2, R304.1
/EXP_RING: D302.1 (A1), J302.2, JP301.2, JP301.5
/EXP_TIP: D301.1 (A1), J302.1, JP301.1, JP301.6
/GND: C101.2, C102.2, C301.2, C302.2, C303.2, D304.2 (A), D306.2 (A), J101.2, J302.3, JP302.1, R101.2, R303.2, R307.2, U301.3 (GND), U301.6 (AIN2), U301.7 (AIN3)
/SCL: J101.4, JP304.2, R305.2
/SDA: J101.3, JP303.2, R306.2
unnamed: C301.1, D303.2 (A), D304.1 (K), R302.2, U301.4 (AIN0)
unnamed: C302.1, D305.2 (A), D306.1 (K), R304.2, U301.5 (AIN1)
unnamed: JP301.3, R302.1, R303.1
unnamed: JP302.2, U301.1 (ADDR)
unnamed: JP303.1, R308.2
unnamed: JP304.1, R309.2
unnamed: R305.1, U301.10 (SCL)
unnamed: R306.1, U301.9 (SDA)

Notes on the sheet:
ARDOR / INDEPENDENT FUNCTION MODULE
Passive expression pedal / I2C ADC / HAND ASSEMBLY
T1 | HAND ASSEMBLY | SEE PIN GUIDE AT RIGHT
Passive 10k-100k pot only. Sleeve = GND. JP301: both shunts 1-3 / 2-4 for tip wiper; 3-5 / 4-6 for ring wiper. JP302: 1-2 = 0x48; 2-3 = 0x49. Never leave ADDR floating. JP303/304 enable local 2.2k I2C pull-ups. Remove BOTH pull-up shunts when host already has pull-ups (Raspberry Pi). Start at 100 k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
PIN GUIDE: IN = into this board / OUT = out / I/O = both / GND = 0 V
J302 / PASSIVE PEDAL
1: TIP I/O 2: RING I/O
3: GND 0V
J101 / PWR IN / I2C
1: 3V3 IN 2: GND 0V
3: DATA I/O 4: CLOCK IN
JP301 / PEDAL JUMPER
1: TIP 2: RING
3: PEDAL IN 4: EXC OUT
5: RING 6: TIP
JP302 / ADDR JUMPER
1: LOW GND 2: SELECT
3: HIGH 3V3
JP303 / DATA PULLUP
1: PULLUP 2: DATA I/O
JP304 / CLOCK PULLUP
1: PULLUP 2: CLOCK IN
U301.2: UNUSED ALERT - LEAVE OPEN / U301.11: BREAKOUT AVDD - LEAVE OPEN / U301.12: BREAKOUT AGND - LEAVE OPEN

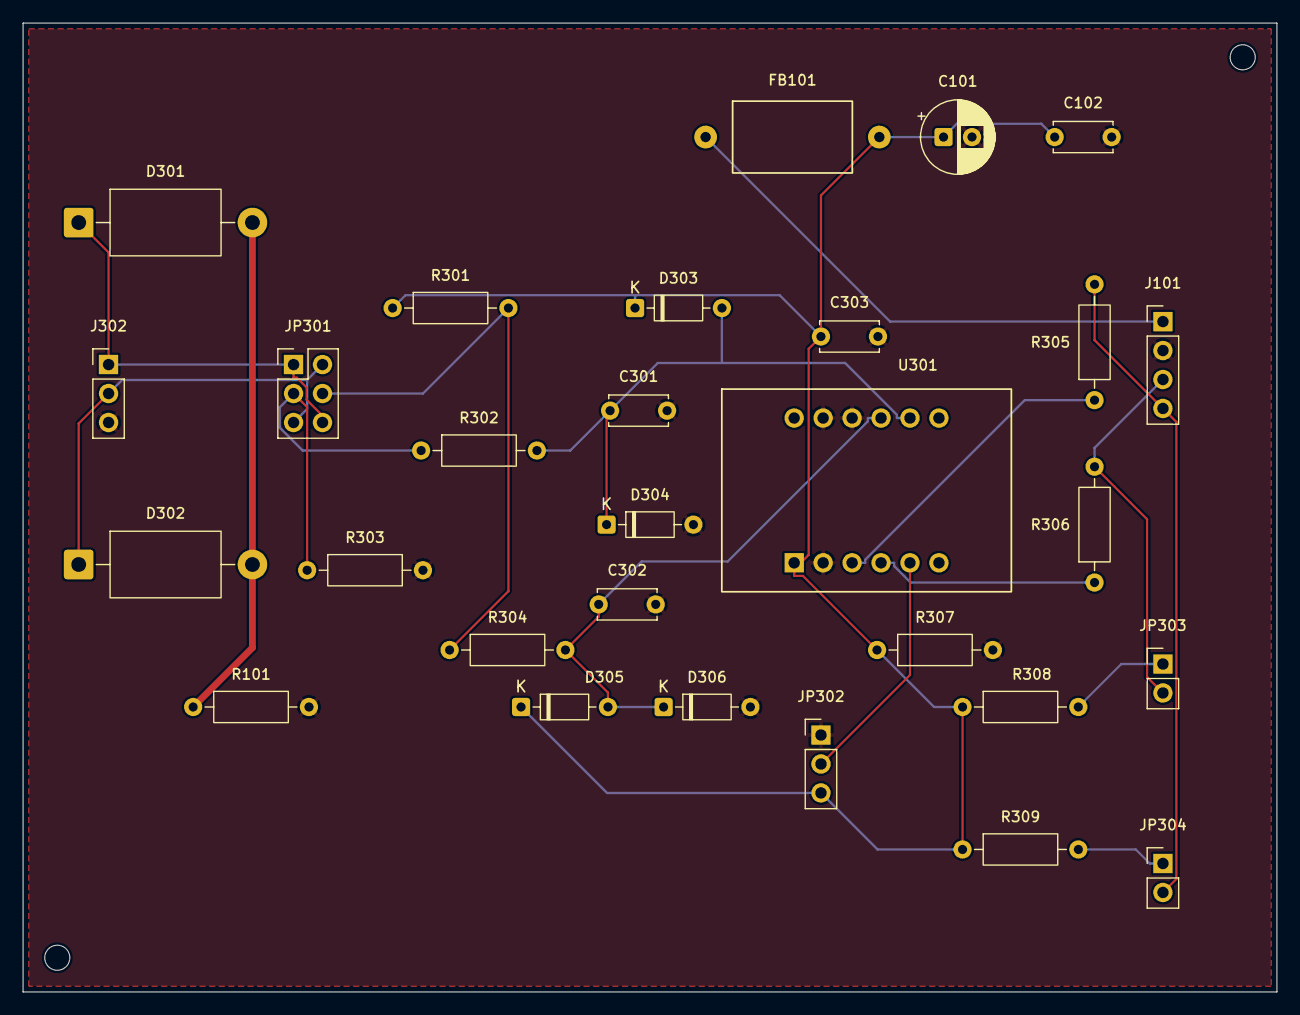
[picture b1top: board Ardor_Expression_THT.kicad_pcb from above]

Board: 2 copper layers, 110.0 x 85.0 mm, 31 parts (0 on the bottom side), 17 nets.

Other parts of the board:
H1, H2: MountingHole_2.2mm_M2

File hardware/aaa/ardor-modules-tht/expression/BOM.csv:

Reference,Value,Footprint,Purchasing specification,Assembly
J302,"PASSIVE PEDAL INPUT / EXCITATION
OUTPUT",Connector_PinHeader_2.54mm:PinHeader_1x03_P2.54mm_Vertical,PinHeader_1x03_P2.54mm_Vertical,THT manual
J101,3V3 POWER INPUT + I2C TO HOST,Connector_PinHeader_2.54mm:PinHeader_1x04_P2.54mm_Vertical,PinHeader_1x04_P2.54mm_Vertical,THT manual
JP301,JUMPER ONLY: PEDAL POLARITY,Connector_PinHeader_2.54mm:PinHeader_2x03_P2.54mm_Vertical,PinHeader_2x03_P2.54mm_Vertical,THT manual
FB101,800R@100MHz / WE 7427501,Ardor_THT:Ferrite_WE_7427501_P15.24mm,Wurth Elektronik 7427501,THT manual
C101,10u / 25V polarized,Capacitor_THT:CP_Radial_D6.3mm_P2.50mm,"Radial electrolytic 10uF 25V, D<=6.3mm P2.5mm",THT manual
C102,100n / 50V X7R,Capacitor_THT:C_Disc_D5.0mm_W2.5mm_P5.00mm,"100nF 50V X7R radial, 5mm lead pitch",THT manual
R301,1kR / 1% 0.25W,Resistor_THT:R_Axial_DIN0207_L6.3mm_D2.5mm_P10.16mm_Horizontal,Axial metal film 1kΩ 1% 0.25W,THT manual
R302,10kR / 1% 0.25W,Resistor_THT:R_Axial_DIN0207_L6.3mm_D2.5mm_P10.16mm_Horizontal,Axial metal film 10kΩ 1% 0.25W,THT manual
R303,1MR / 1% 0.25W,Resistor_THT:R_Axial_DIN0207_L6.3mm_D2.5mm_P10.16mm_Horizontal,Axial metal film 1MΩ 1% 0.25W,THT manual
C301,100n / 50V X7R,Capacitor_THT:C_Disc_D5.0mm_W2.5mm_P5.00mm,"100nF 50V X7R radial, 5mm lead pitch",THT manual
R304,10kR / 1% 0.25W,Resistor_THT:R_Axial_DIN0207_L6.3mm_D2.5mm_P10.16mm_Horizontal,Axial metal film 10kΩ 1% 0.25W,THT manual
C302,100n / 50V X7R,Capacitor_THT:C_Disc_D5.0mm_W2.5mm_P5.00mm,"100nF 50V X7R radial, 5mm lead pitch",THT manual
U301,Adafruit 1085 ADS1115 QT,Ardor_THT:Adafruit_ADS1115_1085_STEMMA_QT,Adafruit 1085 (STEMMA QT revision),Preassembled module; THT sockets
C303,100n / 50V X7R,Capacitor_THT:C_Disc_D5.0mm_W2.5mm_P5.00mm,"100nF 50V X7R radial, 5mm lead pitch",THT manual
R307,2.2kR / 1% 0.25W,Resistor_THT:R_Axial_DIN0207_L6.3mm_D2.5mm_P10.16mm_Horizontal,Axial metal film 2.2kΩ 1% 0.25W,THT manual
D303,BAT85S,Diode_THT:D_DO-35_SOD27_P7.62mm_Horizontal,Vishay BAT85S-TAP,THT manual
D304,BAT85S,Diode_THT:D_DO-35_SOD27_P7.62mm_Horizontal,Vishay BAT85S-TAP,THT manual
D305,BAT85S,Diode_THT:D_DO-35_SOD27_P7.62mm_Horizontal,Vishay BAT85S-TAP,THT manual
D306,BAT85S,Diode_THT:D_DO-35_SOD27_P7.62mm_Horizontal,Vishay BAT85S-TAP,THT manual
R305,33R / 1% 0.25W,Resistor_THT:R_Axial_DIN0207_L6.3mm_D2.5mm_P10.16mm_Horizontal,Axial metal film 33Ω 1% 0.25W,THT manual
R306,33R / 1% 0.25W,Resistor_THT:R_Axial_DIN0207_L6.3mm_D2.5mm_P10.16mm_Horizontal,Axial metal film 33Ω 1% 0.25W,THT manual
JP302,JUMPER ONLY: ADC ADDRESS,Connector_PinHeader_2.54mm:PinHeader_1x03_P2.54mm_Vertical,PinHeader_1x03_P2.54mm_Vertical,THT manual
JP303,JUMPER ONLY: SDA PULLUP,Connector_PinHeader_2.54mm:PinHeader_1x02_P2.54mm_Vertical,PinHeader_1x02_P2.54mm_Vertical,THT manual
JP304,JUMPER ONLY: SCL PULLUP,Connector_PinHeader_2.54mm:PinHeader_1x02_P2.54mm_Vertical,PinHeader_1x02_P2.54mm_Vertical,THT manual
R308,2.2kR / 1% 0.25W,Resistor_THT:R_Axial_DIN0207_L6.3mm_D2.5mm_P10.16mm_Horizontal,Axial metal film 2.2kΩ 1% 0.25W,THT manual
R309,2.2kR / 1% 0.25W,Resistor_THT:R_Axial_DIN0207_L6.3mm_D2.5mm_P10.16mm_Horizontal,Axial metal film 2.2kΩ 1% 0.25W,THT manual
D301,1.5KE6.8CA,Ardor_THT:D_TVS_DC_1.5KE_P15.24mm,DC Components 1.5KE6.8CA (HESTORE 100.430.71),THT manual
D302,1.5KE6.8CA,Ardor_THT:D_TVS_DC_1.5KE_P15.24mm,DC Components 1.5KE6.8CA (HESTORE 100.430.71),THT manual
R101,0R / 1% 0.25W,Resistor_THT:R_Axial_DIN0207_L6.3mm_D2.5mm_P10.16mm_Horizontal,Axial metal film 0Ω 1% 0.25W,THT manual
